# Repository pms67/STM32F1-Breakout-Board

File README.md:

# STM32F1-Breakout-Board
 USB-powered STM32F1-based breakout board. Video: https://www.youtube.com/watch?v=wLwKgMBWhpY

 You can order this board (incl. SMT assembly) at https://www.jlcpcb.com. Gerber and assembly files are in the relevant repo folders.

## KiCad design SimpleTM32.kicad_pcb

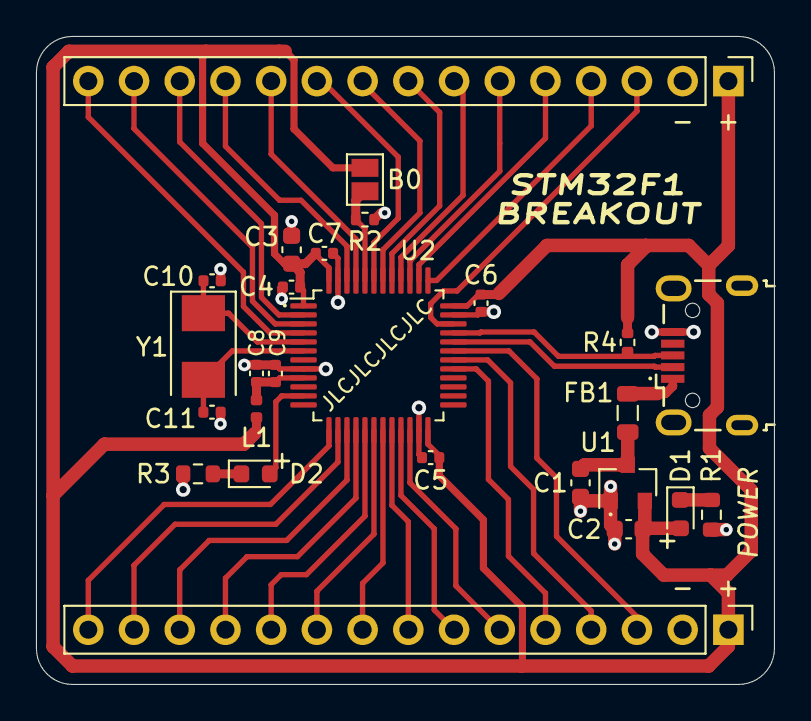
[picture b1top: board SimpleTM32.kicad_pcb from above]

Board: 2 copper layers, 41.0 x 36.0 mm, 26 parts (0 on the bottom side), 39 nets.

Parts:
C1, C2: 1u; C_0603_1608Metric
C3: 4u7; C_0603_1608Metric
C4, C5, C6, C7, C9: 100n; C_0402_1005Metric
C8: 1u; C_0402_1005Metric
C10, C11: 30p; C_0402_1005Metric
D1: GREEN; LED_0603_1608Metric
D2: BLUE; LED_0603_1608Metric
FB1: 100R; L_0805_2012Metric
J1: USB_B_Micro; USB_Micro-B_Wuerth_629105150521
J2, J3: Conn_01x15; PinHeader_1x15_P2.54mm_Vertical
JP1: SolderJumper_2_Open; SolderJumper-2_P1.3mm_Open_Pad1.0x1.5mm
L1: 27n; L_0402_1005Metric
R1, R3: 1k5; R_0603_1608Metric
R2: 10k; R_0402_1005Metric
R4: 1k5; R_0402_1005Metric
U1: XC6206P332MR; SOT-23
U2: STM32F103C8T6; LQFP-48_7x7mm_P0.5mm
Y1: 8MHz; Crystal_SMD_5032-2Pin_5.0x3.2mm

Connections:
+3.3VA: C8.1, C9.1, L1.2, U2.9
+3V3: C2.1, C3.1, C4.1, C5.1, C6.1, C7.1, D1.2, J2.1, J3.1, JP1.1, L1.1, R4.1, U1.2, U2.1, U2.24, U2.36, U2.48
+5V: FB1.2, J1.1
/BOOT0: JP1.2, R2.1, U2.44
/HSE_IN: C11.1, U2.6, Y1.2
/HSE_OUT: C10.1, U2.5, Y1.1
/LED_STAT: D2.2, U2.11
GND: C1.2, C2.2, C3.2, C4.2, C5.2, C6.2, C7.2, C8.2, C9.2, C10.2, C11.2, J1.5, J2.2, J3.2, R1.2, R2.2, R3.2, U1.1, U2.8, U2.23, U2.35, U2.47
unnamed: D1.1, R1.1
unnamed: D2.1, R3.1
PA3: J3.15, U2.13
PA4: J3.14, U2.14
PA5: J3.13, U2.15
PA6: J3.12, U2.16
PA7: J3.11, U2.17
PA8: J3.5, U2.29
PA9: J3.4, U2.30
PA10: J3.3, U2.31
PA15: J2.5, U2.38
PB0: J3.10, U2.18
PB1: J3.9, U2.19
PB2: J3.8, U2.20
PB4: J2.7, U2.40
PB5: J2.8, U2.41
PB6: J2.9, U2.42
PB7: J2.10, U2.43
PB8: J2.11, U2.45
PB9: J2.12, U2.46
PB10: J3.7, U2.21
PB11: J3.6, U2.22
PC13: J2.13, U2.2
PC14: J2.14, U2.3
PC15: J2.15, U2.4
SWCLK: J2.4, U2.37
SWDIO: J2.3, U2.34
SWO: J2.6, U2.39
USB_D+: J1.3, R4.2, U2.33
USB_D-: J1.2, U2.32
VCC: C1.1, FB1.1, U1.3

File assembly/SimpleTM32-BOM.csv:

"Item","Quantity","Designator","Value","LibPart","Footprint","Datasheet","LCSC Part #"
"1","2","C1, C2","1u","Device:C_Small","Capacitor_SMD:C_0603_1608Metric","~","C15849"
"2","1","C3","4u7","Device:C_Small","Capacitor_SMD:C_0603_1608Metric","~","C19666"
"3","5","C4, C5, C6, C7, C9","100n","Device:C_Small","Capacitor_SMD:C_0402_1005Metric","~","C1525"
"4","1","C8","1u","Device:C_Small","Capacitor_SMD:C_0402_1005Metric","~","C52923"
"5","2","C10, C11","30p","Device:C_Small","Capacitor_SMD:C_0402_1005Metric","~","C1570"
"6","1","D1","GREEN","Device:LED_Small","LED_SMD:LED_0603_1608Metric","~","C72043"
"7","1","D2","BLUE","Device:LED_Small","LED_SMD:LED_0603_1608Metric","~","C72041"
"8","1","FB1","100R","Device:Ferrite_Bead_Small","Inductor_SMD:L_0805_2012Metric","~","C1015"
"12","1","L1","27n","Device:L_Small","Inductor_SMD:L_0402_1005Metric","~","C18830"
"13","2","R1, R3","1k5","Device:R_Small","Resistor_SMD:R_0603_1608Metric","~","C22843"
"14","1","R2","10k","Device:R_Small","Resistor_SMD:R_0402_1005Metric","~","C25744"
"15","1","R4","1k5","Device:R_Small","Resistor_SMD:R_0402_1005Metric","~","C25867"
"16","1","U1","XC6206P332MR","Regulator_Linear:XC6206PxxxMR","Package_TO_SOT_SMD:SOT-23","https://www.torexsemi.com/file/xc6206/XC6206.pdf","C5446"
"17","1","U2","STM32F103C8T6","MCU_ST_STM32F1:STM32F103C8Tx","Package_QFP:LQFP-48_7x7mm_P0.5mm","http://www.st.com/st-web-ui/static/active/en/resource/techni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","C8734"
"18","1","Y1","8MHz","Device:Crystal_Small","Crystal:Crystal_SMD_5032-2Pin_5.0x3.2mm","~","C115962"

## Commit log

2020-11-21 Initial commit.
2020-12-05 Fixed empty schematic file.
